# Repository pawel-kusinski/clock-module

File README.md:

# Clock Module
A clock module generating signal with adjustable frequency and with manual pulse trigger mode. It is a part of 8-bit Computer designed by Ben Eater (https://eater.net/8bit/clock). The clock module has been extracted from the original design and laid out on a small PCB which can fit onto breadboards.

The project has been created using KiCad.

More info about this project can be found here <INSERT_LINK>

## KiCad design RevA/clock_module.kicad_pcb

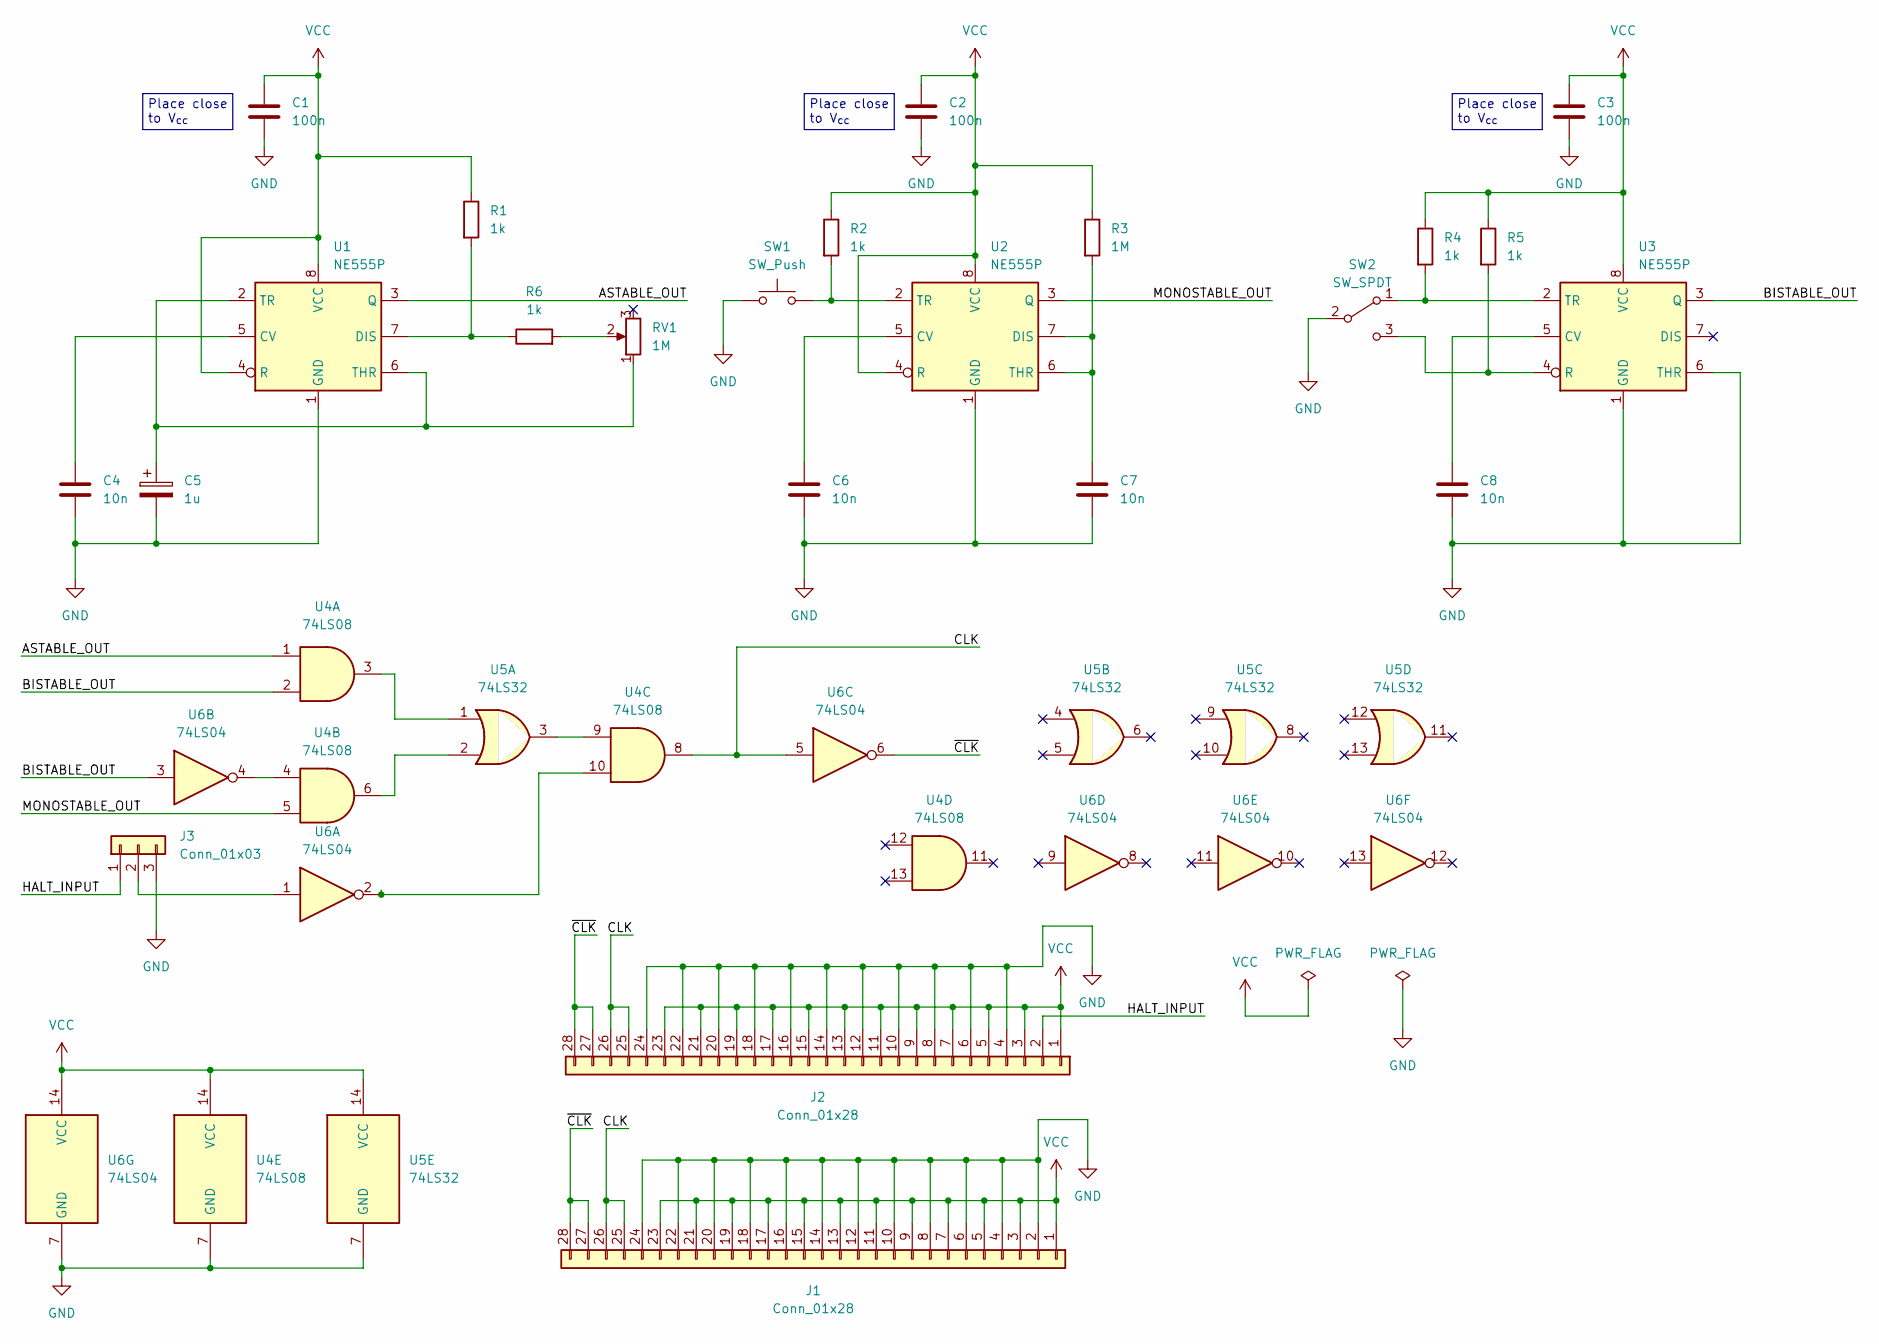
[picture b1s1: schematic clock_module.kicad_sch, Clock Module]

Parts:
C1, C2, C3: 100n; C_0805_2012Metric_Pad1.18x1.45mm_HandSolder
C4, C6, C7, C8: 10n; C_0805_2012Metric_Pad1.18x1.45mm_HandSolder
C5: 1u; CP_Elec_4x5.4
J1, J2: Conn_01x28; PinHeader_1x28_P2.54mm_Vertical
J3: Conn_01x03; PinHeader_1x03_P2.54mm_Vertical
R1, R2, R4, R5, R6: 1k; R_0805_2012Metric_Pad1.20x1.40mm_HandSolder
R3: 1M; R_0805_2012Metric_Pad1.20x1.40mm_HandSolder
RV1: 1M; Potentiometer_Runtron_RM-065_Vertical
SW1: SW_Push; SW_PUSH_6mm
SW2: SW_SPDT; SW_Slide_1P2T_CK_OS102011MS2Q
U1, U2, U3: NE555P; DIP-8_W7.62mm
U4: 74LS08; DIP-14_W7.62mm
U5: 74LS32; DIP-14_W7.62mm
U6: 74LS04; DIP-14_W7.62mm

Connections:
/ASTABLE_OUT: U1.3 (Q), U4.1
/BISTABLE_OUT: U3.3 (Q), U4.2, U6.3
/CLK: J1.25, J1.26, J2.25, J2.26, U4.8, U6.5
/HALT_INPUT: J2.2, J3.1
/MONOSTABLE_OUT: U2.3 (Q), U4.5
/~CLK: J1.27, J1.28, J2.27, J2.28, U6.6
GND: C1.2, C2.2, C3.2, C4.2, C5.2, C6.2, C7.2, C8.2, J1.2, J1.4, J1.6, J1.8, J1.10, J1.12, J1.14, J1.16, J1.18, J1.20, J1.22, J1.24, J2.4, J2.6, J2.8, J2.10, J2.12, J2.14, J2.16, J2.18, J2.20, J2.22, J2.24, J3.3, SW1.1, SW2.2 (B), U1.1 (GND), U2.1 (GND), U3.1 (GND), U3.6 (THR), U4.7 (GND), U5.7 (GND), U6.7 (GND)
unnamed: C4.1, U1.5 (CV)
unnamed: C5.1, RV1.1, U1.2 (TR), U1.6 (THR)
unnamed: C6.1, U2.5 (CV)
unnamed: C7.1, R3.2, U2.6 (THR), U2.7 (DIS)
unnamed: C8.1, U3.5 (CV)
unnamed: R1.2, R6.1, U1.7 (DIS)
unnamed: R2.2, SW1.2, U2.2 (TR)
unnamed: R4.2, SW2.1 (A), U3.2 (TR)
unnamed: R5.2, SW2.3 (C), U3.4 (R)
unnamed: R6.2, RV1.2
unnamed: U4.3, U5.1
unnamed: U4.4, U6.4
unnamed: U4.6, U5.2
unnamed: U4.9, U5.3
unnamed: U4.10, U6.2
unnamed: J3.2, U6.1
VCC: C1.1, C2.1, C3.1, J1.1, J1.3, J1.5, J1.7, J1.9, J1.11, J1.13, J1.15, J1.17, J1.19, J1.21, J1.23, J2.1, J2.3, J2.5, J2.7, J2.9, J2.11, J2.13, J2.15, J2.17, J2.19, J2.21, J2.23, R1.1, R2.1, R3.1, R4.1, R5.1, U1.4 (R), U1.8 (VCC), U2.4 (R), U2.8 (VCC), U3.8 (VCC), U4.14 (VCC), U5.14 (VCC), U6.14 (VCC)

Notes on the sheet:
Place close to V_{cc}

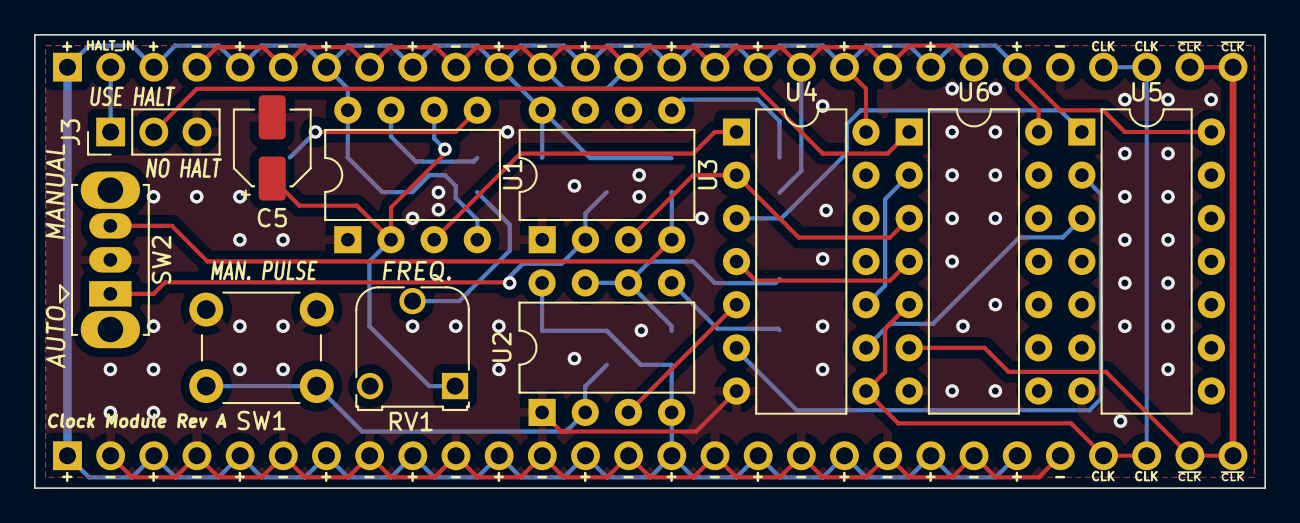
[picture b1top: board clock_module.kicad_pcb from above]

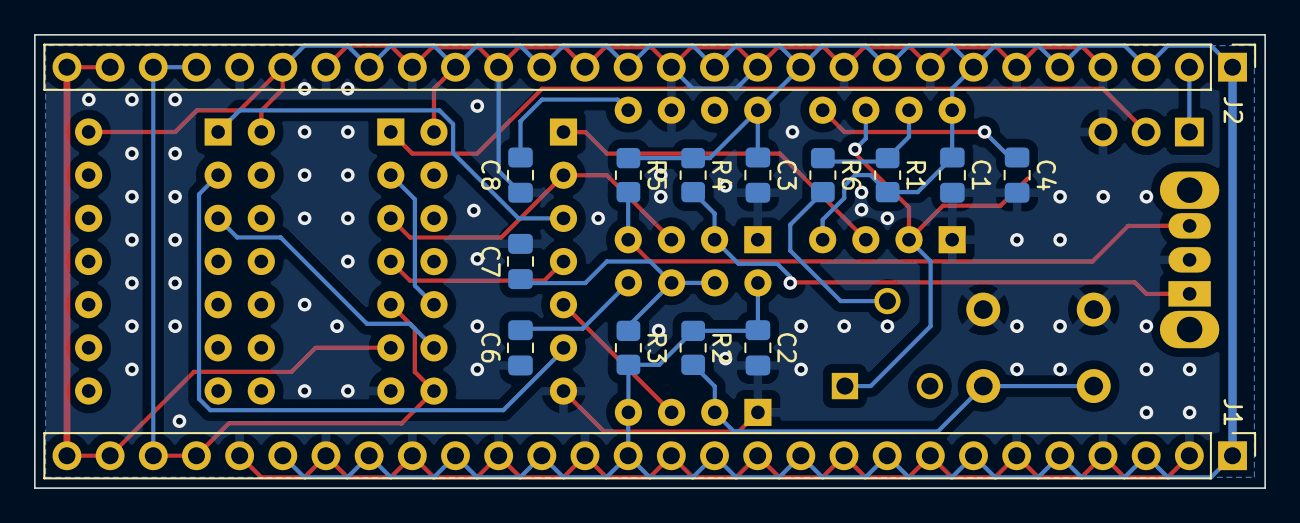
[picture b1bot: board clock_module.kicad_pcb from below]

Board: 2 copper layers, 72.4 x 26.7 mm, 26 parts (15 on the bottom side), 24 nets.
